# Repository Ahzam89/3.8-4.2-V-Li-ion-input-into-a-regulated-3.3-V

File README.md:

# 3.8-4.2-V-Li-ion-input-into-a-regulated-3.3-V
The board converts a single-cell 3.8–4.2 V Li-ion input into a regulated 3.3 V rail supporting up to 500 mA.  This was not simply a matter of placing an LDO between two connectors. The design required careful management of voltage headroom, protection losses, thermal dissipation, transient behavior, grounding, and output stability.

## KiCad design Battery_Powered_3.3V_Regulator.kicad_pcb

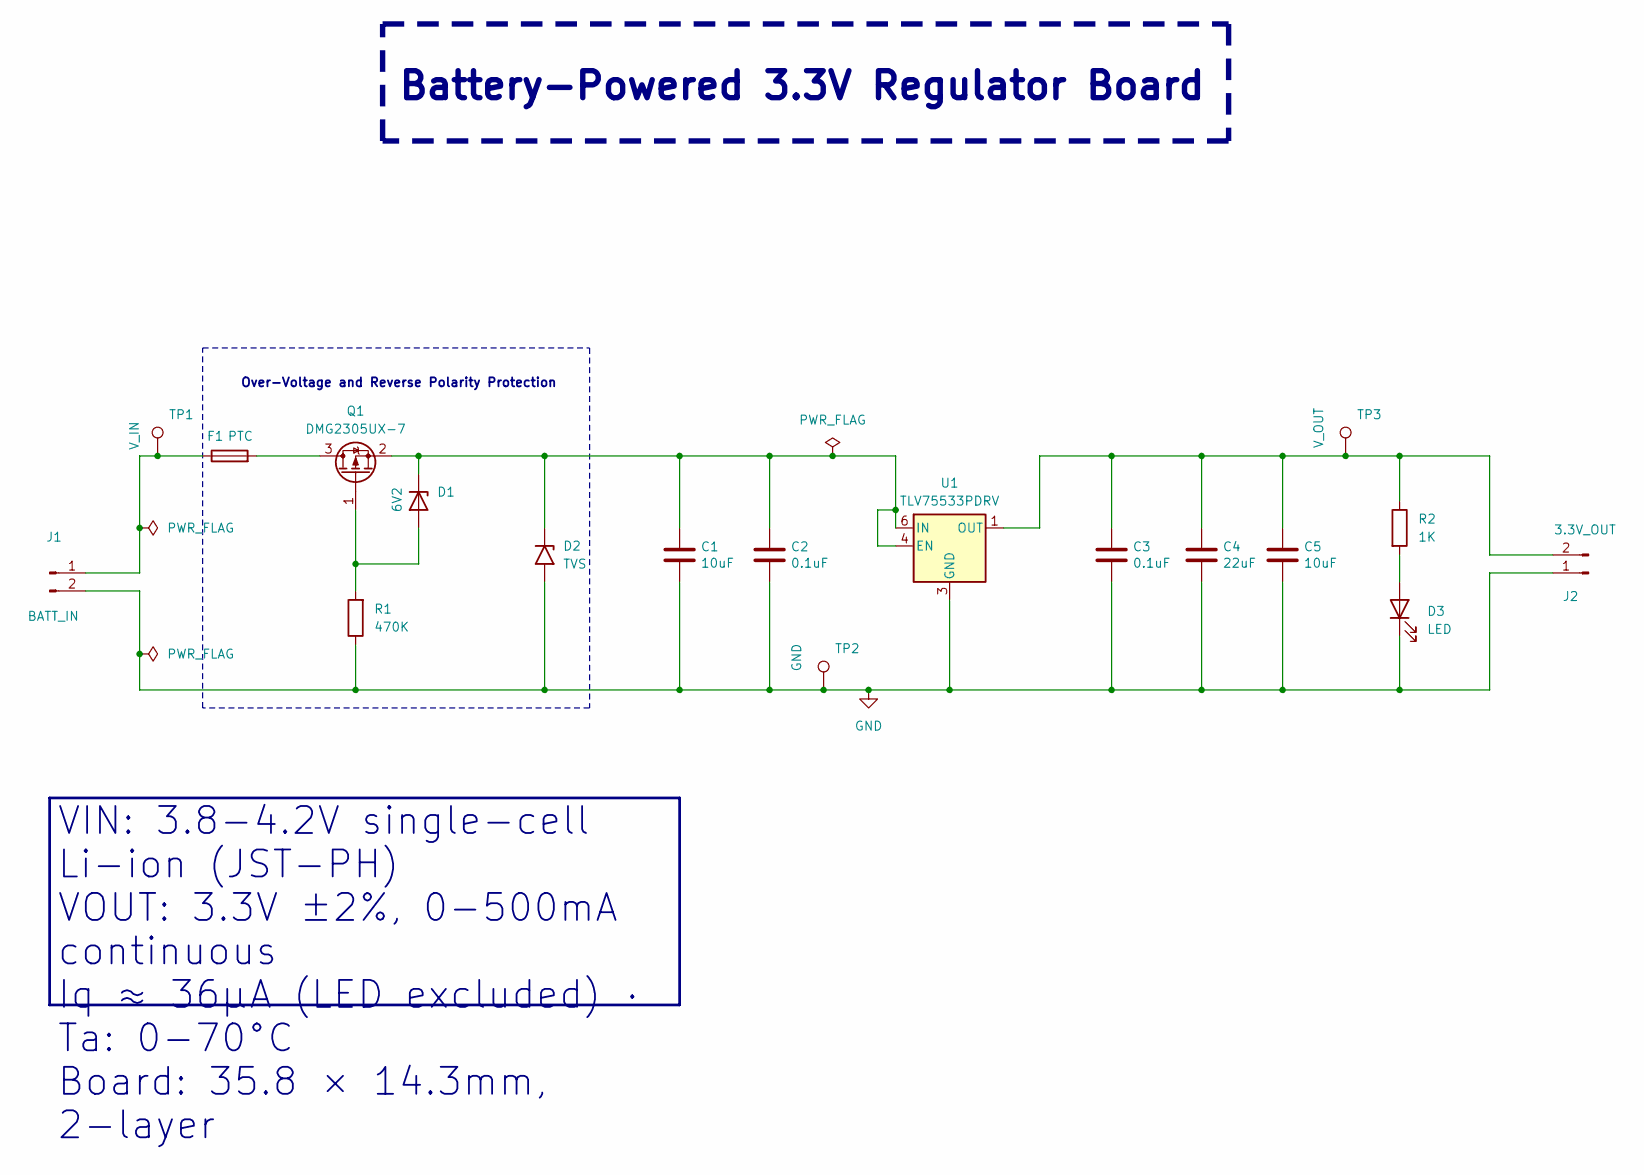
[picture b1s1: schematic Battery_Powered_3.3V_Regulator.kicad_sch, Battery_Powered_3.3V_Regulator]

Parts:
C1, C5: 10uF; C_0805_2012Metric; MPN GRM21BR61C106KE15K
C2, C3: 0.1uF; C_0603_1608Metric; MPN CC0603KRX7R9BB104
C4: 22uF; C_0805_2012Metric; MPN CL21A226MOQNNNE
D1: 6V2; D_SOD-123F; MPN BZT52C6V2-7-F
D2: TVS; D_SMA; MPN SMAJ5.0A
D3: LED; LED_0603_1608Metric; MPN LTST-C190KGKT
F1: PTC; Fuse_1206_3216Metric; MPN 1206L110THYR
J1: BATT_IN; JST_PH_S2B-PH-K_1x02_P2.00mm_Horizontal; MPN S2B-PH-K-S-GW
J2: 3.3V_OUT; PinHeader_1x02_P2.54mm_Horizontal; MPN M20-9750246
Q1: DMG2305UX-7; SOT-23; MPN DMG2305UX-7
R1: 470K; R_0805_2012Metric; MPN RC0805FR-07470KL
R2: 1K; R_0603_1608Metric; MPN CRCW06031K00FKEA
TP1: V_IN; TestPoint_Pad_D1.5mm
TP2: GND; TestPoint_Pad_D1.5mm
TP3: V_OUT; TestPoint_Pad_D1.5mm
U1: TLV75533PDRV; WSON-6-1EP_2x2mm_P0.65mm_EP1x1.6mm; MPN TLV75533PDRVR

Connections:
GND: C1.2, C2.2, C3.2, C4.2, C5.2, D2.2 (A2), D3.1 (K), J1.2, J2.1, R1.1, TP2.1 (1_1), U1.3 (GND), U1.7 (GND)
unnamed: D1.2 (A), Q1.1 (G), R1.2
unnamed: C1.1, C2.1, D1.1 (K), D2.1 (A1), Q1.2 (S), U1.4 (EN), U1.6 (IN)
unnamed: D3.2 (A), R2.2
unnamed: F1.1, J1.1, TP1.1 (1_1)
unnamed: C3.1, C4.1, C5.1, J2.2, R2.1, TP3.1 (1_1), U1.1 (OUT)
unnamed: F1.2, Q1.3 (D)

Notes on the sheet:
Battery-Powered 3.3V Regulator Board
Over-Voltage and Reverse Polarity Protection
VIN: 3.8-4.2V single-cell Li-ion (JST-PH) VOUT: 3.3V ±2%, 0-500mA continuous Iq ≈ 36µA (LED excluded) · Ta: 0-70°C Board: 35.8 × 14.3mm, 2-layer

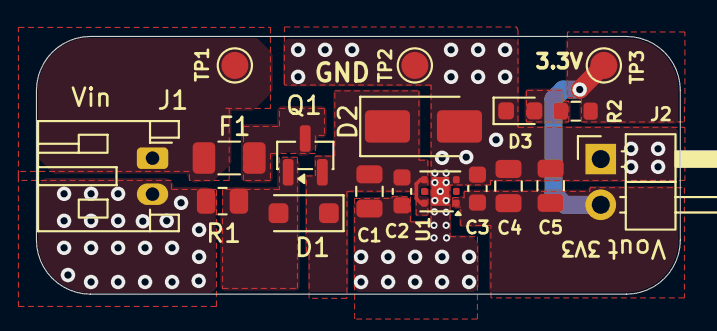
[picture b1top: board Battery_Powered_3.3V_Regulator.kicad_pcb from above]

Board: 2 copper layers, 35.8 x 14.3 mm, 18 parts (0 on the bottom side), 7 nets.

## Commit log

2026-06-21 New_Files
